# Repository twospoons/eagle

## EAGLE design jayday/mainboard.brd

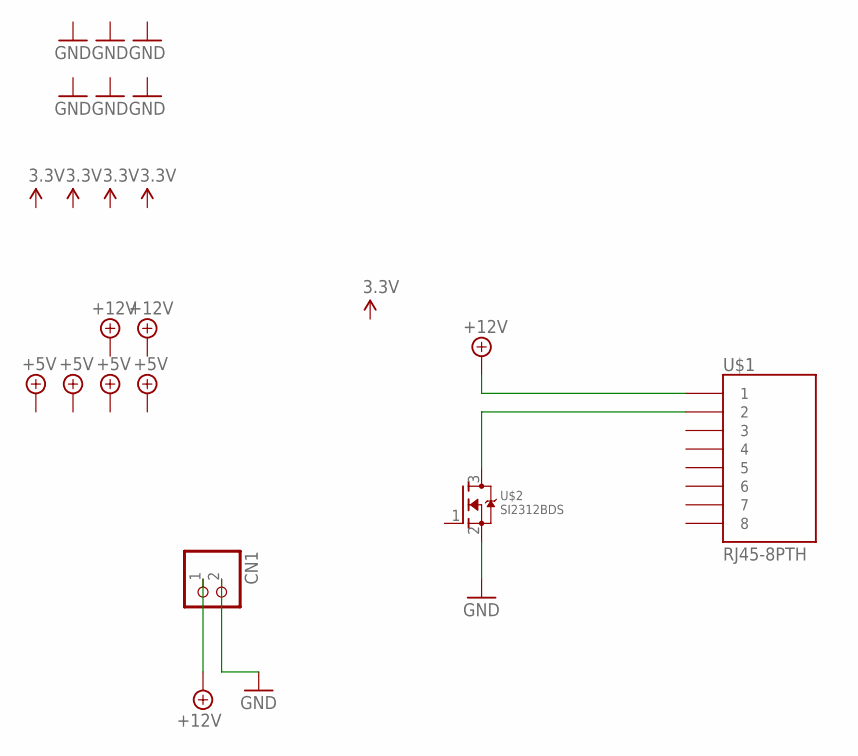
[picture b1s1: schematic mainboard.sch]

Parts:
CN1: JST_2PIN-THM-RA; JST-PH-2-THM-RA
U$1: RJ45-8PTH; RJ45-8
U$2: SI2312BDS; TO-236

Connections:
+12V: U$1.1
GND: CN1.2 (1), U$2.2 (S)
unnamed: U$1.2, U$2.3 (D)

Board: 2 copper layers, 3 parts (0 on the bottom side), 2 nets, no tracks yet.

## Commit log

2012-10-19 inital commit
2012-10-19 added adafruit and sparkfun libraries
2012-10-19 added seeedstudio check files
2012-10-19 moving folders
2012-10-19 renamed folders
2012-10-19 added ozlollc library
2012-10-19 added gadgeteer library
2012-10-19 added eagle design for jayday

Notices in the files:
parts and their libraries:
SparkFun-Connectors: Licensing: CC v3.0 Share-Alike You are welcome to use this library for commercial purposes.
